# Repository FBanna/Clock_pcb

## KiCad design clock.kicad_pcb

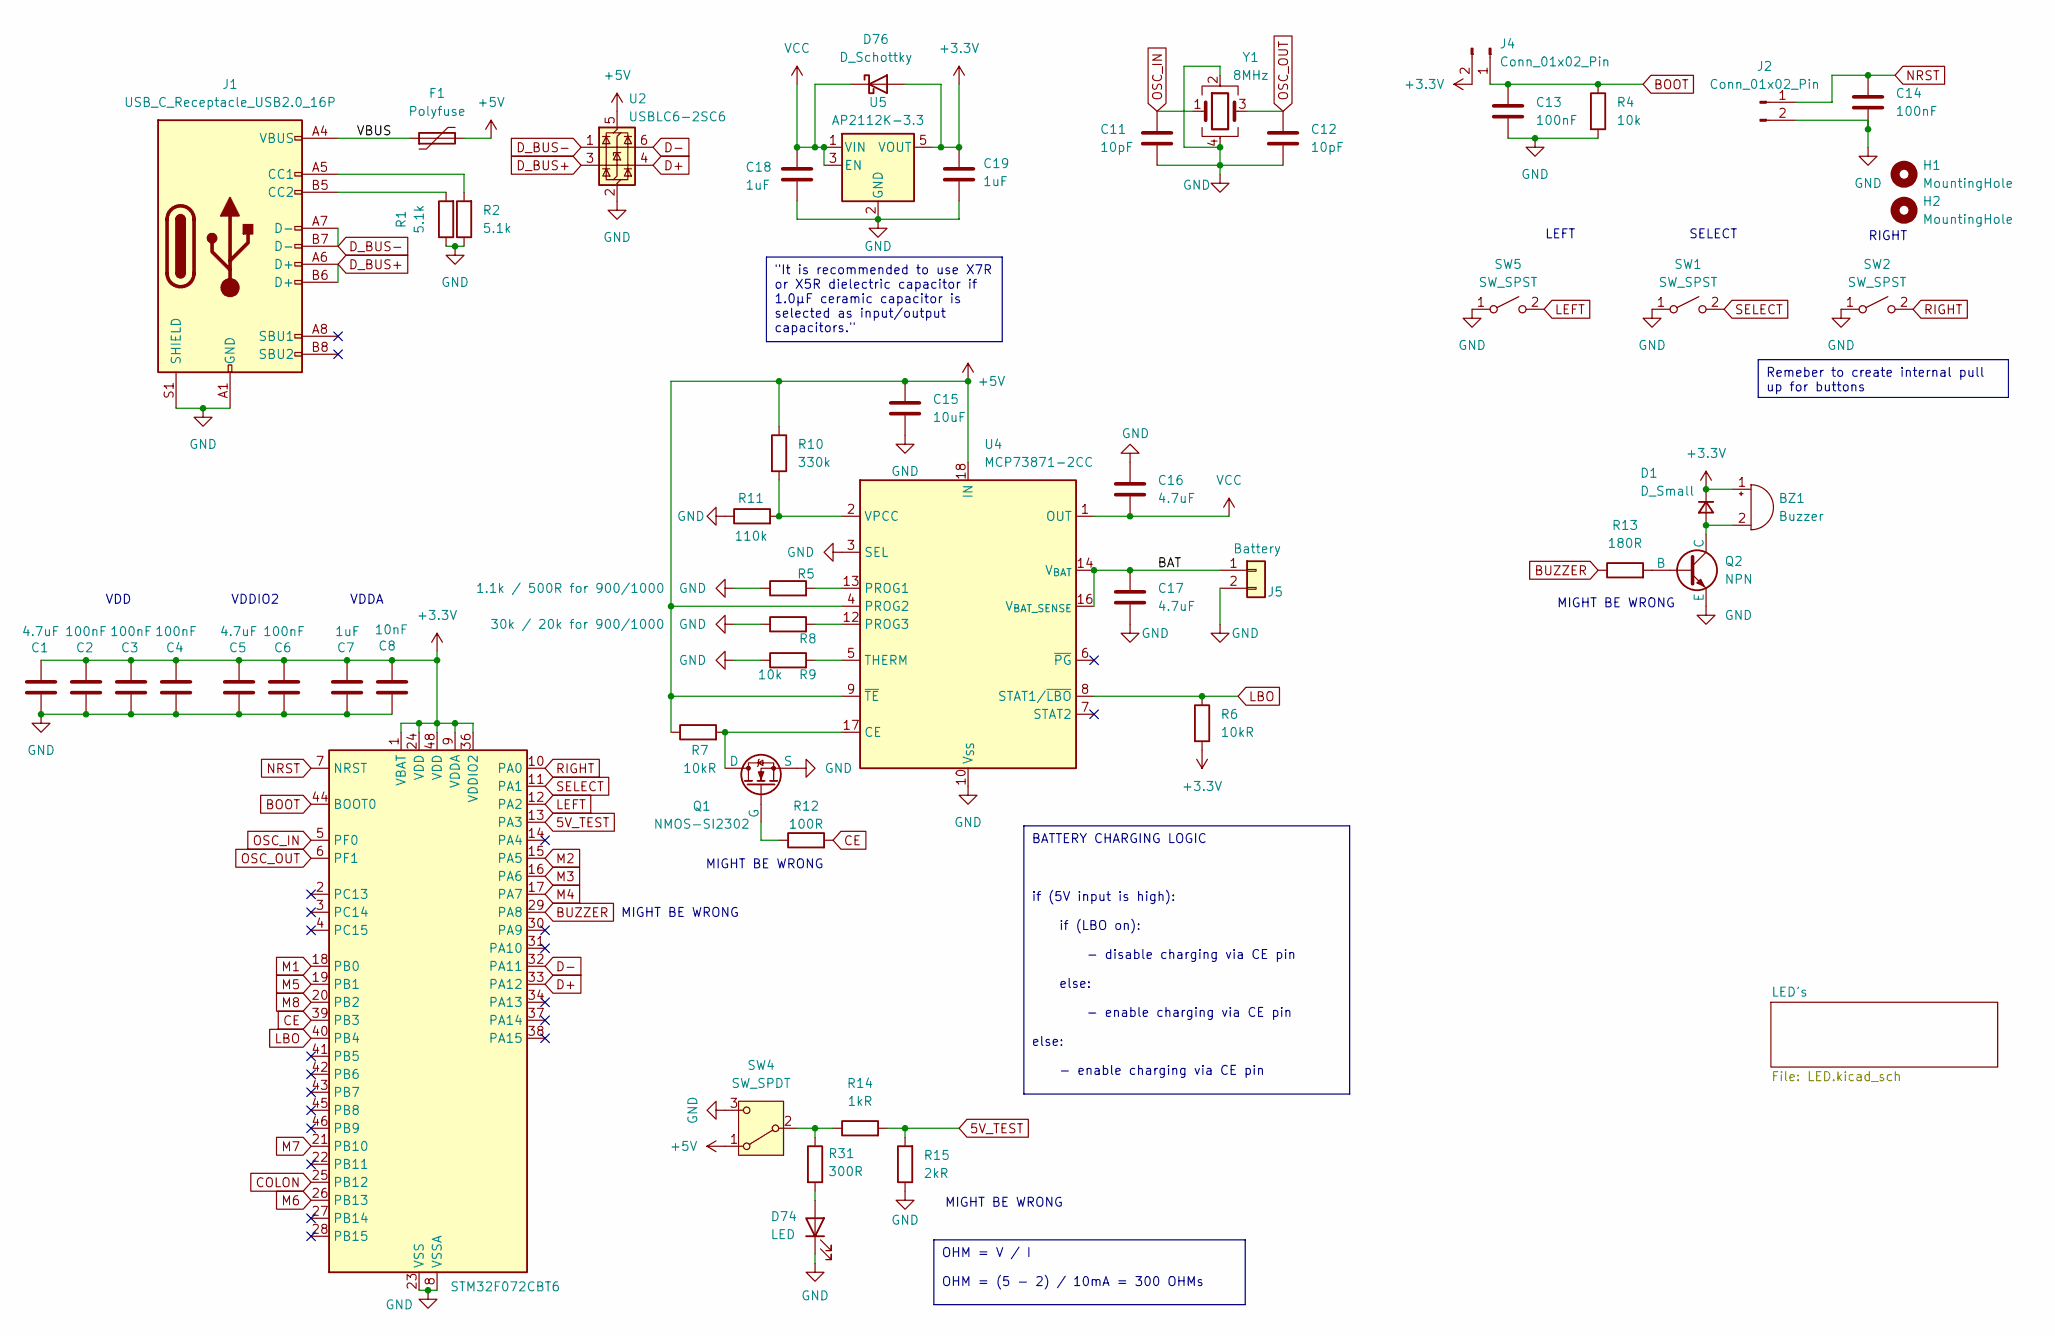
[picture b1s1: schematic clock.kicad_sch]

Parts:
BZ1: Buzzer
C1, C5, C16, C17: 4.7uF; C_0805_2012Metric_Pad1.18x1.45mm_HandSolder
C2, C3, C4, C6, C13, C14: 100nF; C_0402_1005Metric_Pad0.74x0.62mm_HandSolder
C7, C18, C19: 1uF; C_0805_2012Metric_Pad1.18x1.45mm_HandSolder
C8: 10nF; C_0402_1005Metric_Pad0.74x0.62mm_HandSolder
C11, C12: 10pF; C_0402_1005Metric_Pad0.74x0.62mm_HandSolder
C15: 10uF; C_0603_1608Metric_Pad1.08x0.95mm_HandSolder
D1: D_Small; D_SOD-123F
D74: LED; LED_0402_1005Metric_Pad0.77x0.64mm_HandSolder
D76: D_Schottky; D_SOD-123F
F1: Polyfuse; Fuse_0805_2012Metric_Pad1.15x1.40mm_HandSolder
H1, H2: MountingHole; MountingHole_3.2mm_M3
J1: USB_C_Receptacle_USB2.0_16P; USB_C_Receptacle_Palconn_UTC16-G
J2, J4: Conn_01x02_Pin; PinHeader_1x02_P2.54mm_Vertical
J5: Battery; JST_PH_S2B-PH-K_1x02_P2.00mm_Horizontal
Q1: NMOS-SI2302; SOT-23
Q2: NPN; SOT-23_Handsoldering
R1, R2: 5.1k; R_0402_1005Metric_Pad0.72x0.64mm_HandSolder
R4, R9: 10k; R_0402_1005Metric_Pad0.72x0.64mm_HandSolder
R5: 1.1k / 500R for 900/1000; R_0402_1005Metric_Pad0.72x0.64mm_HandSolder
R6, R7: 10kR; R_0402_1005Metric_Pad0.72x0.64mm_HandSolder
R8: 30k / 20k for 900/1000; R_0402_1005Metric_Pad0.72x0.64mm_HandSolder
R10: 330k; R_0402_1005Metric_Pad0.72x0.64mm_HandSolder
R11: 110k; R_0402_1005Metric_Pad0.72x0.64mm_HandSolder
R12: 100R; R_0402_1005Metric_Pad0.72x0.64mm_HandSolder
R13: 180R; R_0402_1005Metric_Pad0.72x0.64mm_HandSolder
R14: 1kR; R_0402_1005Metric_Pad0.72x0.64mm_HandSolder
R15: 2kR; R_0402_1005Metric_Pad0.72x0.64mm_HandSolder
R31: 300R; R_0402_1005Metric_Pad0.72x0.64mm_HandSolder
SW1, SW2, SW5: SW_SPST; SW_push
SW4: SW_SPDT; SW_slide
U1: STM32F072CBT6; LQFP-48_7x7mm_P0.5mm
U2: USBLC6-2SC6; SOT-23-6
U4: MCP73871-2CC; QFN-20-1EP_4x4mm_P0.5mm_EP2.5x2.5mm
U5: AP2112K-3.3; SOT-23-5
Y1: 8MHz; Crystal_SMD_3225-4Pin_3.2x2.5mm_HandSoldering

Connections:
5V_TEST: R14.2, R15.2, U1.13 (PA3)
+3.3V: BZ1.1 (+), C1.1, C2.1, C3.1, C4.1, C5.1, C6.1, C7.1, C8.1, C19.1, D1.1 (K), D76.2 (A), J4.2, R6.2, U1.1 (VBAT), U1.9 (VDDA), U1.24 (VDD), U1.36 (VDDIO2), U1.48 (VDD), U5.5 (VOUT)
+5V: C15.1, F1.2, R7.1, R10.1, SW4.1 (A), U2.5 (VBUS), U4.4 (PROG2), U4.9 (~TE), U4.18 (IN), U4.19 (IN)
/BAT: C17.1, J5.1, U4.14 (V_{BAT}), U4.15 (V_{BAT}), U4.16 (V_{BAT_SENSE})
/VBUS: F1.1, J1.A4 (VBUS), J1.A9 (VBUS), J1.B4 (VBUS), J1.B9 (VBUS)
BOOT: C13.1, J4.1, R4.1, U1.44 (BOOT0)
BUZZER: R13.1, U1.29 (PA8)
CE: R12.2, U1.39 (PB3)
COLON: U1.25 (PB12); also elsewhere on the board
D+: U1.33 (PA12), U2.4 (I/O2)
D-: U1.32 (PA11), U2.6 (I/O1)
D_BUS+: J1.A6 (D+), J1.B6 (D+), U2.3 (I/O2)
D_BUS-: J1.A7 (D-), J1.B7 (D-), U2.1 (I/O1)
GND: C1.2, C2.2, C3.2, C4.2, C5.2, C6.2, C7.2, C8.2, C11.2, C12.2, C13.2, C14.2, C15.2, C16.1, C17.2, C18.2, C19.2, D74.1 (K), J1.A1 (GND), J1.A12 (GND), J1.B1 (GND), J1.B12 (GND), J1.S1 (SHIELD), J2.2, J5.2, Q1.3 (S), Q2.3 (E), R1.1, R2.1, R4.2, R5.1, R8.1, R9.1, R11.1, R15.1, SW1.1 (A), SW2.1 (A), SW4.3 (C), SW5.1 (A), U1.8 (VSSA), U1.23 (VSS), U1.35 (VSS), U1.47 (VSS), U2.2 (GND), U4.3 (SEL), U4.10 (V_{SS}), U4.11 (V_{SS}), U4.21 (V_{SS}), U5.2 (GND), Y1.2, Y1.4; also elsewhere on the board
LBO: R6.1, U1.40 (PB4), U4.8 (STAT1/~LBO)
LEFT: SW5.2 (B), U1.12 (PA2)
M1: U1.18 (PB0); also elsewhere on the board
M2: U1.15 (PA5); also elsewhere on the board
M3: U1.16 (PA6); also elsewhere on the board
M4: U1.17 (PA7); also elsewhere on the board
M5: U1.19 (PB1); also elsewhere on the board
M6: U1.26 (PB13); also elsewhere on the board
M7: U1.21 (PB10); also elsewhere on the board
M8: U1.20 (PB2); also elsewhere on the board
NRST: C14.1, J2.1, U1.7 (NRST)
unnamed: BZ1.2 (-), D1.2 (A), Q2.1 (C)
unnamed: D74.2 (A), R31.2
unnamed: J1.A5 (CC1), R2.2
unnamed: J1.B5 (CC2), R1.2
unnamed: Q1.1 (D), R7.2, U4.17 (CE)
unnamed: Q1.2 (G), R12.1
unnamed: Q2.2 (B), R13.2
unnamed: R14.1, R31.1, SW4.2 (B)
unnamed: R5.2, U4.13 (PROG1)
unnamed: R8.2, U4.12 (PROG3)
unnamed: R9.2, U4.5 (THERM)
unnamed: R10.2, R11.2, U4.2 (VPCC)
OSC_IN: C11.1, U1.5 (PF0), Y1.1
OSC_OUT: C12.1, U1.6 (PF1), Y1.3
RIGHT: SW2.2 (B), U1.10 (PA0)
SELECT: SW1.2 (B), U1.11 (PA1)
VCC: C16.2, C18.1, D76.1 (K), U4.1 (OUT), U4.20 (OUT), U5.1 (VIN), U5.3 (EN)

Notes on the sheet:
BATTERY CHARGING LOGIC if (5V input is high): if (LBO on): - disable charging via CE pin else: - enable charging via CE pin else: - enable charging via CE pin
Remeber to create internal pull up for buttons
OHM = V / I OHM = (5 - 2) / 10mA = 300 OHMs
"It is recommended to use X7R or X5R dielectric capacitor if 1.0µF ceramic capacitor is selected as input/output capacitors."
VDD
VDDIO2
MIGHT BE WRONG
VDDA
SELECT
LEFT
RIGHT

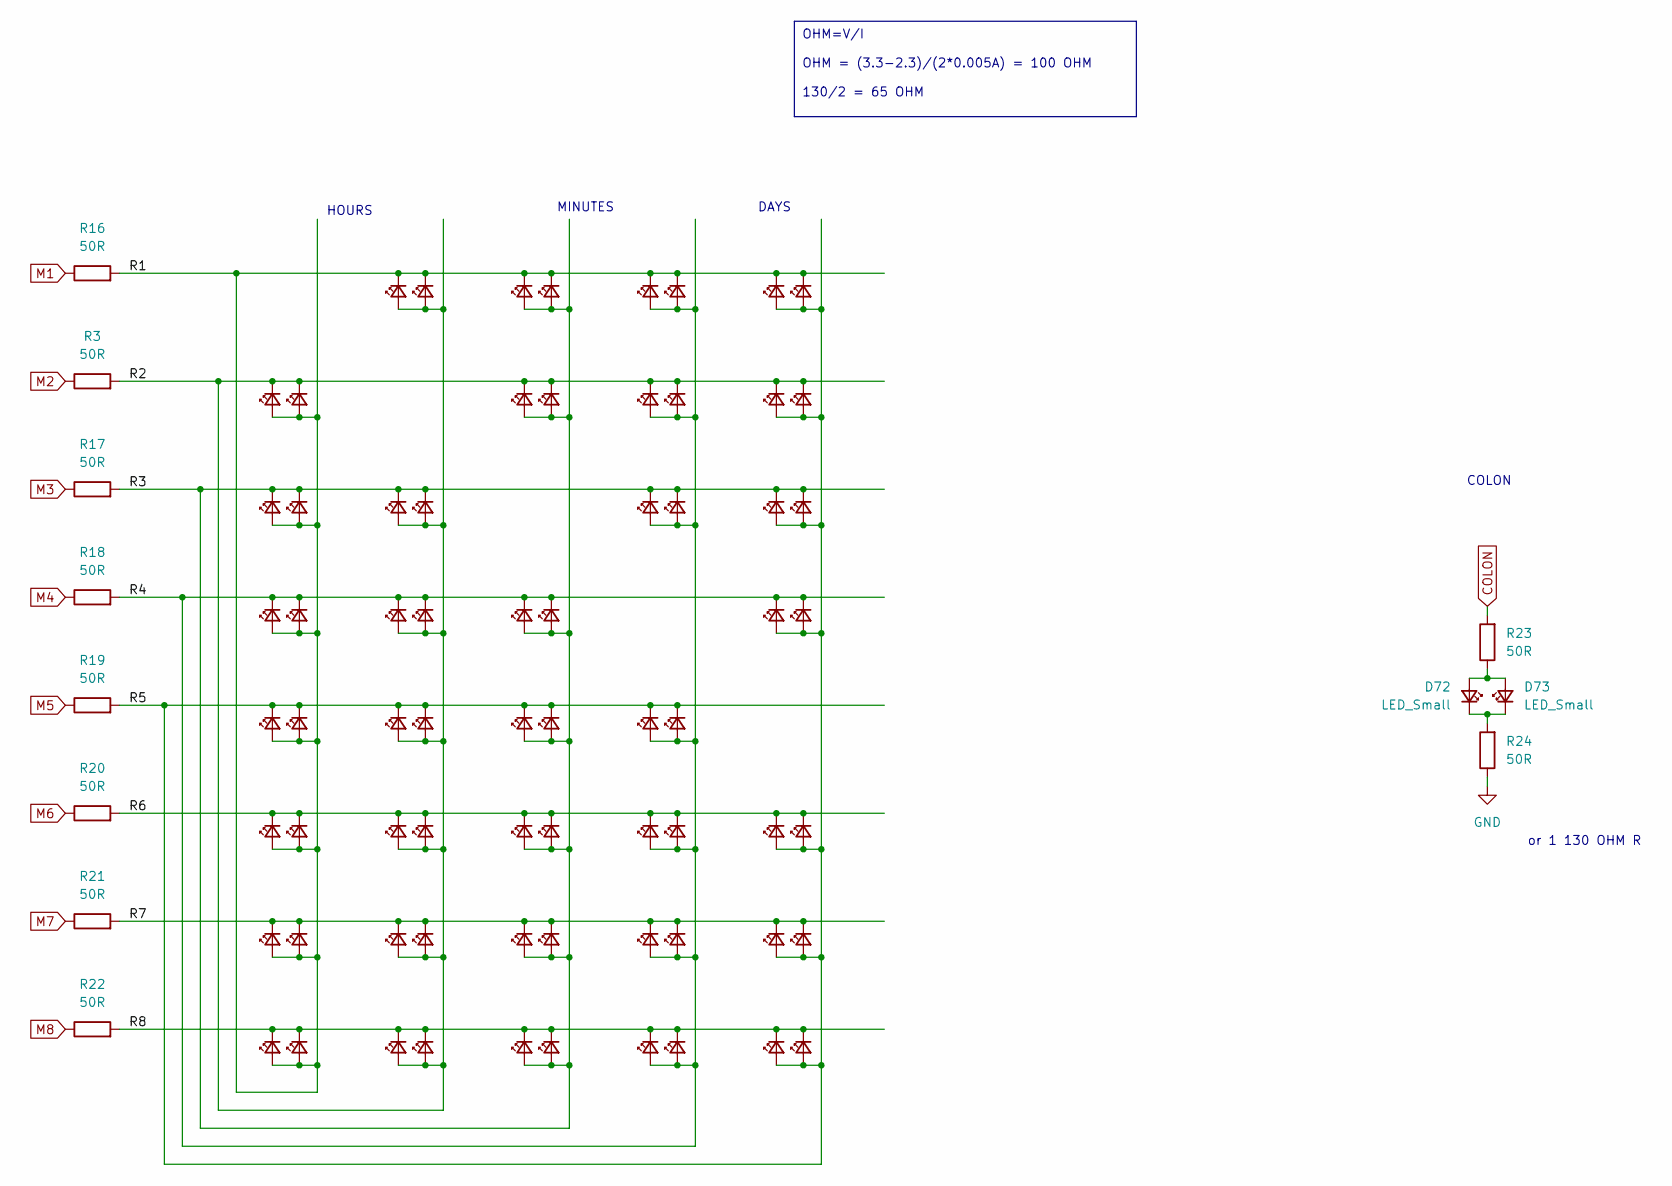
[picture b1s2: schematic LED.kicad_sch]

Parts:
D2, D3, D4, D5, D6, D7, D8, D9, D10, D11, D12, D13, D14, D15, D16, D17, D18, D19, D20, D21, D22, D23, D24, D25, D26, D27, D28, D29, D30, D31, D32, D33, D34, D35, D36, D37, D38, D39, D40, D41, D42, D43, D44, D45, D46, D47, D48, D49, D50, D51, D52, D53, D54, D55, D56, D57, D58, D59, D60, D61, D62, D63, D64, D65, D66, D67, D68, D69, D70, D71, D72, D73: LED_Small; LED_0402_1005Metric_Pad0.77x0.64mm_HandSolder
R3, R16, R17, R18, R19, R20, R21, R22, R23, R24: 50R; R_0402_1005Metric_Pad0.72x0.64mm_HandSolder

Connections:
/LED's/R1: D2.2 (A), D3.2 (A), D4.2 (A), D5.2 (A), D6.2 (A), D7.2 (A), D8.2 (A), D9.2 (A), D10.2 (A), D11.2 (A), D12.2 (A), D13.2 (A), D14.2 (A), D15.2 (A), D16.1 (K), D23.1 (K), D30.1 (K), D37.1 (K), D44.1 (K), D51.1 (K), D58.1 (K), D65.1 (K), R16.2
/LED's/R2: D2.1 (K), D9.1 (K), D16.2 (A), D17.2 (A), D18.2 (A), D19.2 (A), D20.2 (A), D21.2 (A), D22.2 (A), D23.2 (A), D24.2 (A), D25.2 (A), D26.2 (A), D27.2 (A), D28.2 (A), D29.2 (A), D31.1 (K), D38.1 (K), D45.1 (K), D52.1 (K), D59.1 (K), D66.1 (K), R3.2
/LED's/R3: D3.1 (K), D10.1 (K), D17.1 (K), D24.1 (K), D30.2 (A), D31.2 (A), D32.2 (A), D33.2 (A), D34.2 (A), D35.2 (A), D36.2 (A), D37.2 (A), D38.2 (A), D39.2 (A), D40.2 (A), D41.2 (A), D42.2 (A), D43.2 (A), D46.1 (K), D53.1 (K), D60.1 (K), D67.1 (K), R17.2
/LED's/R4: D4.1 (K), D11.1 (K), D18.1 (K), D25.1 (K), D32.1 (K), D39.1 (K), D44.2 (A), D45.2 (A), D46.2 (A), D47.2 (A), D48.2 (A), D49.2 (A), D50.2 (A), D51.2 (A), D52.2 (A), D53.2 (A), D54.2 (A), D55.2 (A), D56.2 (A), D57.2 (A), D61.1 (K), D68.1 (K), R18.2
/LED's/R5: D5.1 (K), D12.1 (K), D19.1 (K), D26.1 (K), D33.1 (K), D40.1 (K), D47.1 (K), D54.1 (K), D58.2 (A), D59.2 (A), D60.2 (A), D61.2 (A), D62.2 (A), D63.2 (A), D64.2 (A), D65.2 (A), D66.2 (A), D67.2 (A), D68.2 (A), D69.2 (A), D70.2 (A), D71.2 (A), R19.2
/LED's/R6: D6.1 (K), D13.1 (K), D20.1 (K), D27.1 (K), D34.1 (K), D41.1 (K), D48.1 (K), D55.1 (K), D62.1 (K), D69.1 (K), R20.2
/LED's/R7: D7.1 (K), D14.1 (K), D21.1 (K), D28.1 (K), D35.1 (K), D42.1 (K), D49.1 (K), D56.1 (K), D63.1 (K), D70.1 (K), R21.2
/LED's/R8: D8.1 (K), D15.1 (K), D22.1 (K), D29.1 (K), D36.1 (K), D43.1 (K), D50.1 (K), D57.1 (K), D64.1 (K), D71.1 (K), R22.2
COLON: R23.2; also elsewhere on the board
GND: R24.1; also elsewhere on the board
M1: R16.1; also elsewhere on the board
M2: R3.1; also elsewhere on the board
M3: R17.1; also elsewhere on the board
M4: R18.1; also elsewhere on the board
M5: R19.1; also elsewhere on the board
M6: R20.1; also elsewhere on the board
M7: R21.1; also elsewhere on the board
M8: R22.1; also elsewhere on the board
unnamed: D72.2 (A), D73.2 (A), R23.1
unnamed: D72.1 (K), D73.1 (K), R24.2

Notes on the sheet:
OHM=V/I OHM = (3.3-2.3)/(2*0.005A) = 100 OHM 130/2 = 65 OHM
HOURS
MINUTES
DAYS
COLON
or 1 130 OHM R

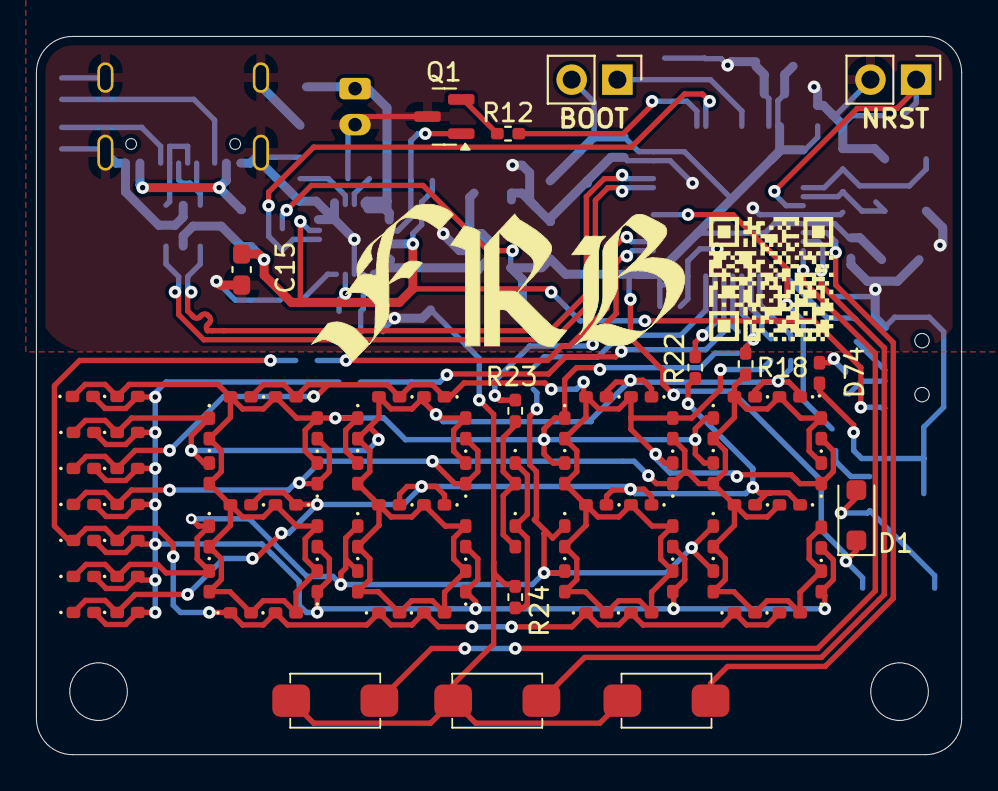
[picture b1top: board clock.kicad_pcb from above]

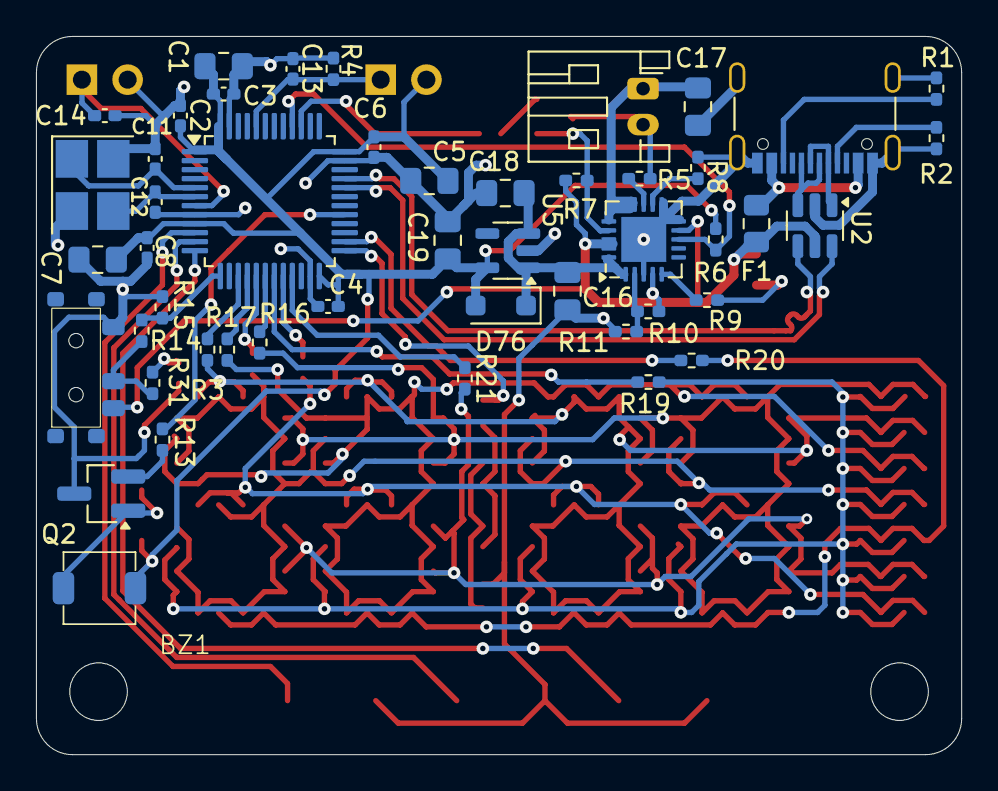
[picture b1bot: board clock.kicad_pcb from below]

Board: 2 copper layers, 51.4 x 39.9 mm, 136 parts (48 on the bottom side), 52 nets.

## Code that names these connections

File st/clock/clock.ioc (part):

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Mcu.Name=STM32F072C(8-B)Tx
Mcu.Package=LQFP48
Mcu.UserName=STM32F072CBTx
PA0.GPIOParameters=GPIO_Label
PA0.GPIO_Label=RIGHT
PA0.Signal=GPIO_Input
PA1.GPIOParameters=GPIO_Label
PA1.GPIO_Label=SELECT
PA1.Signal=GPIO_Input
PA11.Mode=Device
PA11.Signal=USB_DM
PA12.Mode=Device
PA12.Signal=USB_DP
PA2.GPIOParameters=GPIO_Label
PA2.GPIO_Label=LEFT
PA2.Signal=GPIO_Input
PA3.GPIOParameters=GPIO_Label
PA3.GPIO_Label=FV_TEST
PA3.Signal=GPIO_Input
PA4.GPIOParameters=GPIO_Label
PA4.GPIO_Label=BUZZER
PA4.Signal=GPIO_Output
PA5.GPIOParameters=GPIO_Label
PA5.GPIO_Label=M2
PA5.Signal=GPIO_Output
PA6.GPIOParameters=GPIO_Label
PA6.GPIO_Label=M3
PA6.Signal=GPIO_Output
PA7.GPIOParameters=GPIO_Label
PA7.GPIO_Label=M4
PA7.Signal=GPIO_Output
PA8.Signal=S_TIM1_CH1
PB0.GPIOParameters=GPIO_Label
PB0.GPIO_Label=M1
PB0.Signal=GPIO_Output
PB1.GPIOParameters=GPIO_Label
PB1.GPIO_Label=M5
PB1.Signal=GPIO_Output
PB10.GPIOParameters=GPIO_Label
PB10.GPIO_Label=M7
PB10.Signal=GPIO_Output
PB12.GPIOParameters=GPIO_Label
PB12.GPIO_Label=COLON
PB12.Signal=GPIO_Output
PB13.GPIOParameters=GPIO_Label
PB13.GPIO_Label=M6
PB13.Signal=GPIO_Output
PB2.GPIOParameters=GPIO_Label
PB2.GPIO_Label=M8
PB2.Signal=GPIO_Output
PB3.GPIOParameters=GPIO_Label
PB3.GPIO_Label=CE
PB3.Signal=GPIO_Input
PB4.GPIOParameters=GPIO_Label
PB4.GPIO_Label=LBO
PB4.Signal=GPIO_Input
PF0-OSC_IN.Mode=HSE-External-Oscillator
PF0-OSC_IN.Signal=RCC_OSC_IN
PF1-OSC_OUT.Mode=HSE-External-Oscillator
PF1-OSC_OUT.Signal=RCC_OSC_OUT
RCC.SYSCLKFreq_VALUE=16000000
RCC.SYSCLKSource=RCC_SYSCLKSOURCE_PLLCLK
board=custom

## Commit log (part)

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2024-10-29 init
2024-11-03 stuff?
2024-11-03 hooked up switches
2024-11-04 started adding charging ic
2024-11-04 nothing really
2024-11-05 changed resistor value
2024-11-08 most of the charging ic set up
2024-11-19 litteraly nothing
2025-01-09 added some r
2025-01-24 new st cube ide files
2025-01-24 deleted some resistors
2025-01-24 pull up resistor
2025-01-26 lots of changes, circuit to disable chip now works (Ihope)
2025-01-27 st files + voltage divider
2025-01-30 new resistors for LED matrix
2025-01-30 actually grounded STM, changed charlie plexed resistors, added note for charging logic, added switch for the 5V logic detection
2025-01-31 added lables for buttons
2025-01-31 done loads, added indication LED, changed how switches works, added footprints for lots of things, set up editor for laying things out
2025-02-01 action
2025-02-01 started layout, redid the crystal
2025-02-01 layed out the LED display
2025-02-01 more layout
2025-02-02 first attempt at layout
2025-02-03 changed R package sizes + moved stuff around
2025-02-03 readme
2025-02-03 all done with action
2025-02-04 small routing changes, reverted action change
2025-02-04 routing attempt again
2025-02-04 built net
2025-02-05 rerouting to flip the usb to the other side
2025-02-06 more routing
2025-02-06 flipped routing now has ground plane
2025-02-06 more routing, diff pair, 3V3 to chip etc.
2025-02-07 routing
2025-02-07 charlie plex routing
2025-02-07 buttons in place + missing M8 connection
2025-02-08 am I ok??? is this too close. Nearly done!! mabye..
2025-02-08 fixed weird kicad bug, added last few components, just need to add charlie plexed resistors + wire it up
2025-02-09 all wiring done, need to clean up silk screen edge clips + double check pins for charlieplex & buttons
2025-02-10 fixed overlap of silkscreen
2025-02-10 st cube pin assignments
2025-02-11 swapped mosfet need to fix buzzer
2025-02-12 beginning buzzer changes
2025-02-13 changed it ig
2025-02-14 idk again
2025-02-14 looking good, changed buzzer, changed buzzer pin, changed resistors, changed stcube ide config
2025-02-16 changed resistor values
2025-02-16 silk screen additions
2025-02-17 moved qr code
2025-02-17 sent off for production, added a few GND vias, put NRST and BOOT silkscreen on the front
2025-02-18 changed usb model to export to fusion
2025-02-23 temp
2025-02-28 code????
2025-02-28 code?????
2025-02-28 coding?????????????????????
2025-03-01 registry changes
2025-03-02 lots of prgamming changes
2025-03-03 added flashing colon & selected digits
2025-03-03 5V test
2025-03-03 more coding added sleep
2025-03-04 5V stuff
2025-03-04 added CE stuff, added alarm setting page (doesnt trigger yet???)
2025-03-06 alarm might work now
2025-03-06 alarms working
2025-08-16 idk what i changed
